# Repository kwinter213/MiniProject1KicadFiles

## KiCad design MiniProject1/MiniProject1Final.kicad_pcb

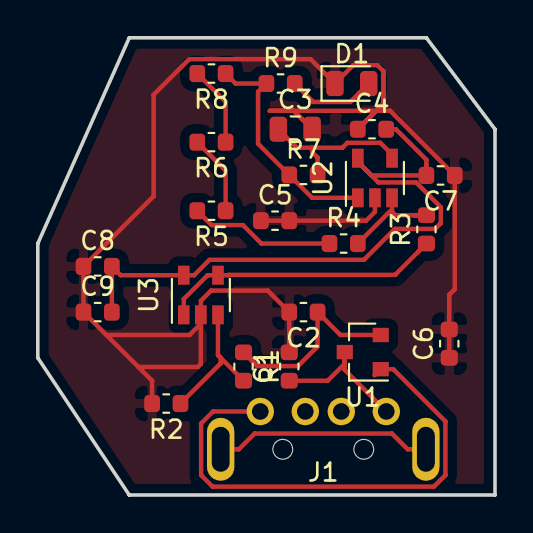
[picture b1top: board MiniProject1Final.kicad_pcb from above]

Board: 2 copper layers, 25.4 x 25.4 mm, 23 parts (0 on the bottom side), 14 nets.

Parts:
C1, C2: 1 u; C_0603_1608Metric
C3: .1 u; C_0805_2012Metric
C4, C5, C8: .1 u; C_0603_1608Metric
C6, C7, C9: 1 n; C_0603_1608Metric
D1: LED; LED_0805_2012Metric
J1: USB_A; USBA
R1, R2: 4.02 k; R_0603_1608Metric
R3, R8: 100; R_0603_1608Metric
R4: 30.1; R_0603_1608Metric
R5: 20; R_0603_1608Metric
R6: 158; R_0603_1608Metric
R7: 10 k; R_0603_1608Metric
R9: 806; R_0603_1608Metric
U1: LinearReg; SOT-23
U2, U3: OpAmp; SOT-23-5

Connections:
+3V3: C4.2, C7.2, C8.2, C9.2, U2.5, U3.5
GND: C1.2, C2.2, C3.2, C4.1, C5.1, C5.2, C6.1, C6.2, C7.1, C8.1, C9.1, D1.1, R2.2, U2.2, U3.2
unnamed: C1.1, J1.1, U1.3
unnamed: C2.1, R1.1, U1.2
unnamed: C3.1, R7.2, U2.4
unnamed: D1.2, R9.2
unnamed: J1.4, U1.1
unnamed: R1.2, R2.1, U3.3
unnamed: R3.1, U3.1, U3.4
unnamed: R3.2, R4.2, U2.3
unnamed: R4.1, R5.2
unnamed: R5.1, R6.2
unnamed: R6.1, R8.2
unnamed: R7.1, R8.1, R9.1, U2.1

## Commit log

2019-02-11 All KiCad files
    All KiCad files that contributed to my first ever(!) PCB. Credit to Bradley Minch, Coleman Ellis, Paige Pfenninger, and helpful friends along the way (Annie Kroo, Adam Selker, Maximilian Schommer)
2019-02-11 Fixed bypass caps
2019-02-11 Fixed resistors with updated LTSpice model
    Switched Capacitor/resistor
2019-02-11 Fixed RC values
